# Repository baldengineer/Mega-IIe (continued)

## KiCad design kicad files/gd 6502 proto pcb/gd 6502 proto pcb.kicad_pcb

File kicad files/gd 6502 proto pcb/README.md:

## gd 6502 proto pcb
6502 board is designed for a WDC W65c02 with a QFP footprint. It has a single socket for an EPROM and is wired like the IIc's EEPROM. The `Address` and `Data` headers are meant to connect to the MEGA-II proto board. Other control signals are broken out to other headers.

Runs off of 5V.

## Rev1 Notes:
* Nothing... yet :)

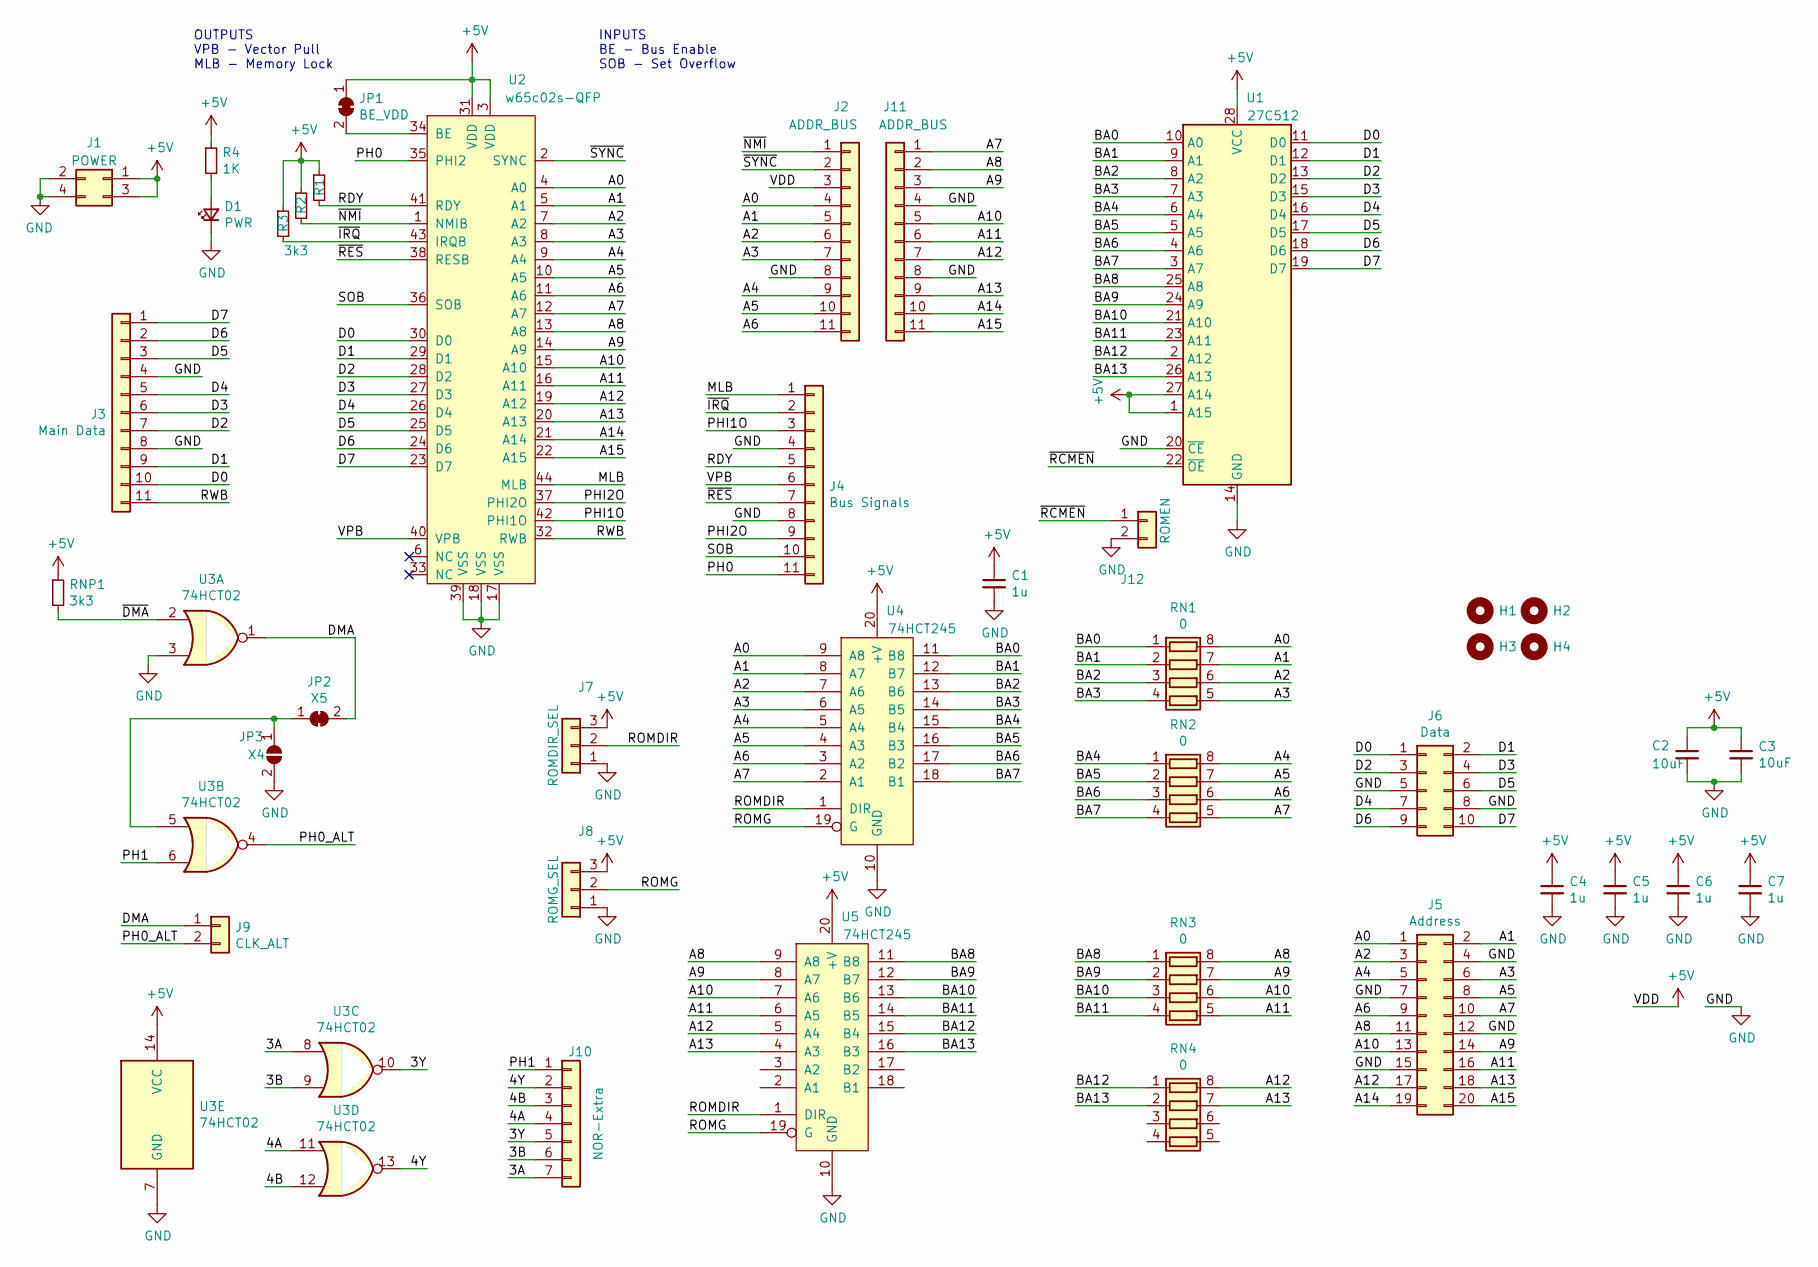
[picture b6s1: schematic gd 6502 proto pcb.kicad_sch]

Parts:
C1, C4, C5, C6, C7: 1u; C_0805_2012Metric
C2: 10uF; C_Radial_D6.3mm_H5.0mm_P2.50mm
C3: 10uF; C_0805_2012Metric
D1: PWR; D_1206_3216Metric
H1, H2, H3, H4: MountingHole; MountingHole_2.7mm_M2.5
J1: POWER; PinHeader_2x02_P2.54mm_Vertical
J2, J11: ADDR_BUS; PinHeader_1x11_P2.54mm_Vertical
J3: Main Data; PinHeader_1x11_P2.54mm_Vertical
J4: Bus Signals; PinHeader_1x11_P2.54mm_Vertical
J5: Address; PinHeader_2x10_P2.54mm_Vertical
J6: Data; PinHeader_2x05_P2.54mm_Vertical
J7: ROMDIR_SEL; PinHeader_1x03_P2.54mm_Vertical
J8: ROMG_SEL; PinHeader_1x03_P2.54mm_Vertical
J9: CLK_ALT; PinHeader_1x02_P2.54mm_Vertical
J10: NOR-Extra; PinHeader_1x07_P2.54mm_Vertical
J12: ROMEN; PinHeader_1x02_P2.54mm_Vertical
JP1: BE_VDD; SolderJumper-2_P1.3mm_Bridged_Pad1.0x1.5mm
JP2: X5; SolderJumper-2_P1.3mm_Bridged_Pad1.0x1.5mm
JP3: X4; SolderJumper-2_P1.3mm_Open_RoundedPad1.0x1.5mm
R1, R2, R3: 3k3; R_0805_2012Metric
R4: 1K; R_0805_2012Metric
RN1, RN2, RN3, RN4: 0; R_Array_Convex_4x0612
RNP1: 3k3; R_0805_2012Metric
U1: 27C512; DIP-28_W15.24mm_Socket_LongPads
U2: w65c02s-QFP; PQFP-44_10x10mm_P0.8mm
U3: 74HCT02; SOIC-14_3.9x8.7mm_P1.27mm
U4, U5: 74HCT245; SOIC-20W_7.5x12.8mm_P1.27mm

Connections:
+5V: C1.1, C2.1, C3.1, C4.1, C5.1, C6.1, C7.1, J1.1, J1.3, J2.3, J7.3, J8.3, JP1.1 (A), R1.1, R2.1, R3.1, R4.1, RNP1.1, U1.1 (A15), U1.27 (A14), U1.28 (VCC), U2.3 (VDD), U2.31 (VDD), U3.14 (VCC), U4.20 (+V), U5.20 (+V)
/3A: J10.7, U3.8
/3B: J10.6, U3.9
/3Y: J10.5, U3.10
/4A: J10.4, U3.11
/4B: J10.3, U3.12
/4Y: J10.2, U3.13
/A0: J2.4, J5.1, RN1.8 (R1.2), U2.4 (A0), U4.9 (A8)
/A1: J2.5, J5.2, RN1.7 (R2.2), U2.5 (A1), U4.8 (A7)
/A2: J2.6, J5.3, RN1.6 (R3.2), U2.7 (A2), U4.7 (A6)
/A3: J2.7, J5.6, RN1.5 (R4.2), U2.8 (A3), U4.6 (A5)
/A4: J2.9, J5.5, RN2.8 (R1.2), U2.9 (A4), U4.5 (A4)
/A5: J2.10, J5.8, RN2.7 (R2.2), U2.10 (A5), U4.4 (A3)
/A6: J2.11, J5.9, RN2.6 (R3.2), U2.11 (A6), U4.3 (A2)
/A7: J5.10, J11.1, RN2.5 (R4.2), U2.12 (A7), U4.2 (A1)
/A8: J5.11, J11.2, RN3.8 (R1.2), U2.13 (A8), U5.9 (A8)
/A9: J5.14, J11.3, RN3.7 (R2.2), U2.14 (A9), U5.8 (A7)
/A10: J5.13, J11.5, RN3.6 (R3.2), U2.15 (A10), U5.7 (A6)
/A11: J5.16, J11.6, RN3.5 (R4.2), U2.16 (A11), U5.6 (A5)
/A12: J5.17, J11.7, RN4.8 (R1.2), U2.19 (A12), U5.5 (A4)
/A13: J5.18, J11.9, RN4.7 (R2.2), U2.20 (A13), U5.4 (A3)
/A14: J5.19, J11.10, U2.21 (A14)
/A15: J5.20, J11.11, U2.22 (A15)
/BA0: RN1.1 (R1.1), U1.10 (A0), U4.11 (B8)
/BA1: RN1.2 (R2.1), U1.9 (A1), U4.12 (B7)
/BA2: RN1.3 (R3.1), U1.8 (A2), U4.13 (B6)
/BA3: RN1.4 (R4.1), U1.7 (A3), U4.14 (B5)
/BA4: RN2.1 (R1.1), U1.6 (A4), U4.15 (B4)
/BA5: RN2.2 (R2.1), U1.5 (A5), U4.16 (B3)
/BA6: RN2.3 (R3.1), U1.4 (A6), U4.17 (B2)
/BA7: RN2.4 (R4.1), U1.3 (A7), U4.18 (B1)
/BA8: RN3.1 (R1.1), U1.25 (A8), U5.11 (B8)
/BA9: RN3.2 (R2.1), U1.24 (A9), U5.12 (B7)
/BA10: RN3.3 (R3.1), U1.21 (A10), U5.13 (B6)
/BA11: RN3.4 (R4.1), U1.23 (A11), U5.14 (B5)
/BA12: RN4.1 (R1.1), U1.2 (A12), U5.15 (B4)
/BA13: RN4.2 (R2.1), U1.26 (A13), U5.16 (B3)
/D0: J3.10, J6.1, U1.11 (D0), U2.30 (D0)
/D1: J3.9, J6.2, U1.12 (D1), U2.29 (D1)
/D2: J3.7, J6.3, U1.13 (D2), U2.28 (D2)
/D3: J3.6, J6.4, U1.15 (D3), U2.27 (D3)
/D4: J3.5, J6.7, U1.16 (D4), U2.26 (D4)
/D5: J3.3, J6.6, U1.17 (D5), U2.25 (D5)
/D6: J3.2, J6.9, U1.18 (D6), U2.24 (D6)
/D7: J3.1, J6.10, U1.19 (D7), U2.23 (D7)
/DMA: J9.1, JP2.2 (B), U3.1
/MLB: J4.1, U2.44 (MLB)
/PH0: J4.11, U2.35 (PHI2)
/PH0_ALT: J9.2, U3.4
/PH1: J10.1, U3.6
/PHI1O: J4.3, U2.42 (PHI1O)
/PHI2O: J4.9, U2.37 (PHI2O)
/RDY: J4.5, R1.2, U2.41 (RDY)
/ROMDIR: J7.2, U4.1 (DIR), U5.1 (DIR)
/ROMG: J8.2, U4.19 (G), U5.19 (G)
/RWB: J3.11, U2.32 (RWB)
/SOB: J4.10, U2.36 (SOB)
/VPB: J4.6, U2.40 (VPB)
/~DMA: RNP1.2, U3.2
/~IRQ: J4.2, R3.2, U2.43 (IRQB)
/~NMI: J2.1, R2.2, U2.1 (NMIB)
/~RCMEN: J12.1, U1.22 (~OE)
/~RES: J4.7, U2.38 (RESB)
/~SYNC: J2.2, U2.2 (SYNC)
GND: C1.2, C2.2, C3.2, C4.2, C5.2, C6.2, C7.2, D1.1 (K), J1.2, J1.4, J2.8, J3.4, J3.8, J4.4, J4.8, J5.4, J5.7, J5.12, J5.15, J6.5, J6.8, J7.1, J8.1, J11.4, J11.8, J12.2, JP3.2 (B), U1.14 (GND), U1.20 (~CE), U2.17 (VSS), U2.18 (VSS), U2.39 (VSS), U3.3, U3.7 (GND), U4.10 (GND), U5.10 (GND)
unnamed: D1.2 (A), R4.2
unnamed: JP1.2 (B), U2.34 (BE)
unnamed: JP2.1 (A), JP3.1 (A), U3.5

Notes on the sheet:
INPUTS BE - Bus Enable SOB - Set Overflow
OUTPUTS VPB - Vector Pull MLB - Memory Lock

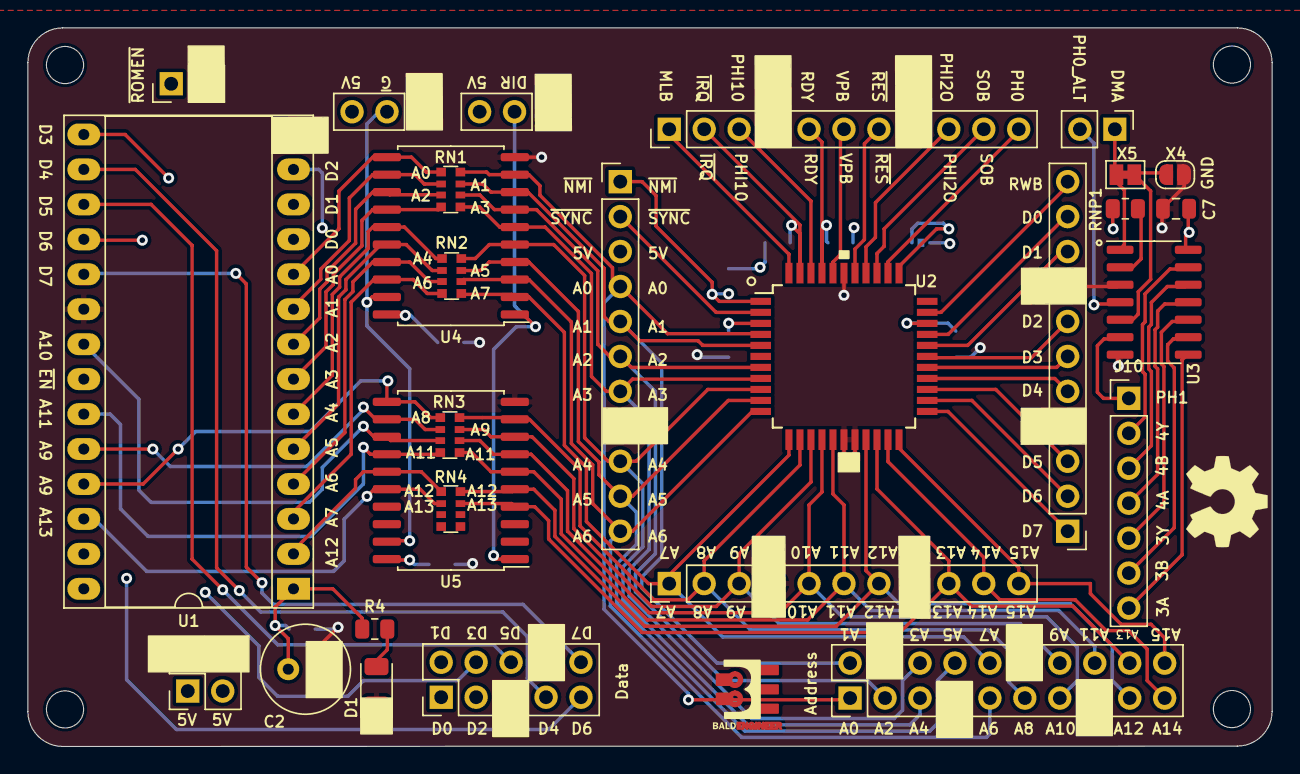
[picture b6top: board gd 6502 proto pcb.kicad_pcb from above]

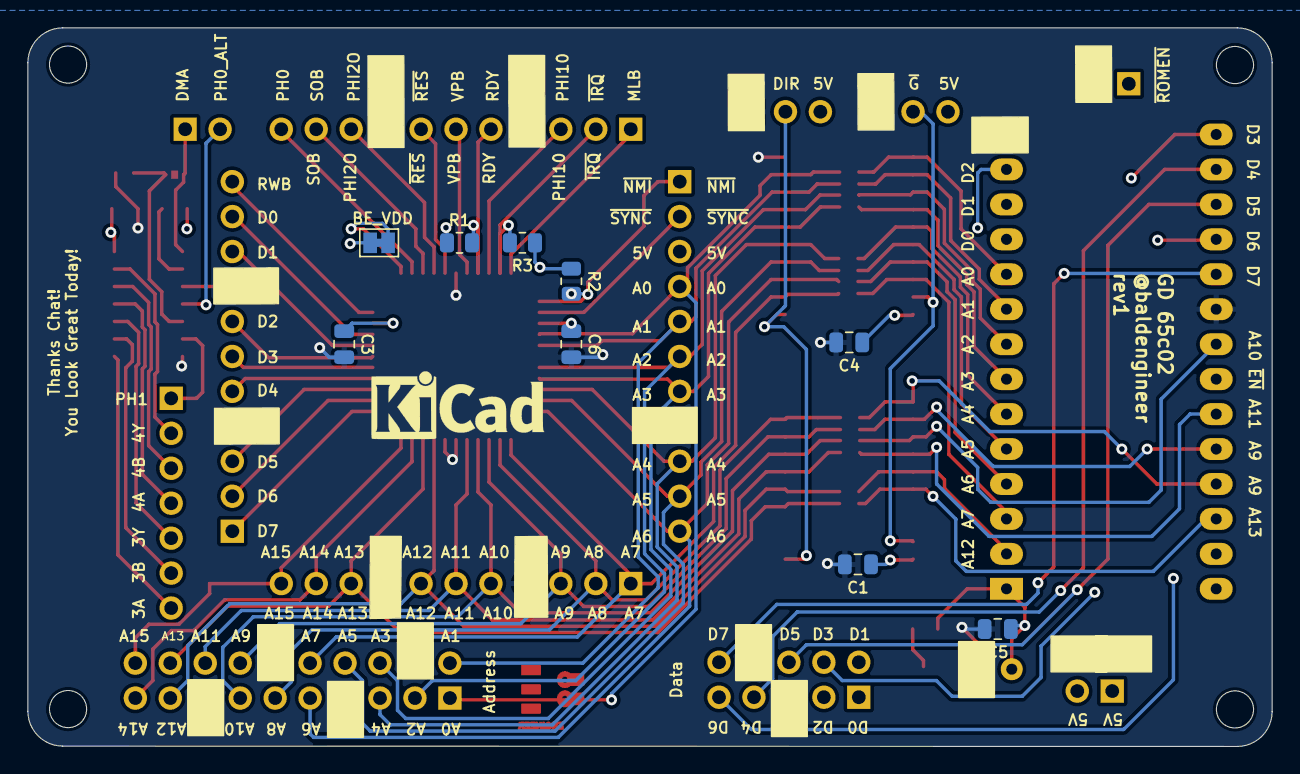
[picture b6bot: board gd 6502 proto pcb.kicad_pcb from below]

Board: 4 copper layers, 90.4 x 52.2 mm, 42 parts (9 on the bottom side), 68 nets.

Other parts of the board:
He: MountingHole; MountingHole_2.7mm_M2.5
svg2mod: G***; BE5v2

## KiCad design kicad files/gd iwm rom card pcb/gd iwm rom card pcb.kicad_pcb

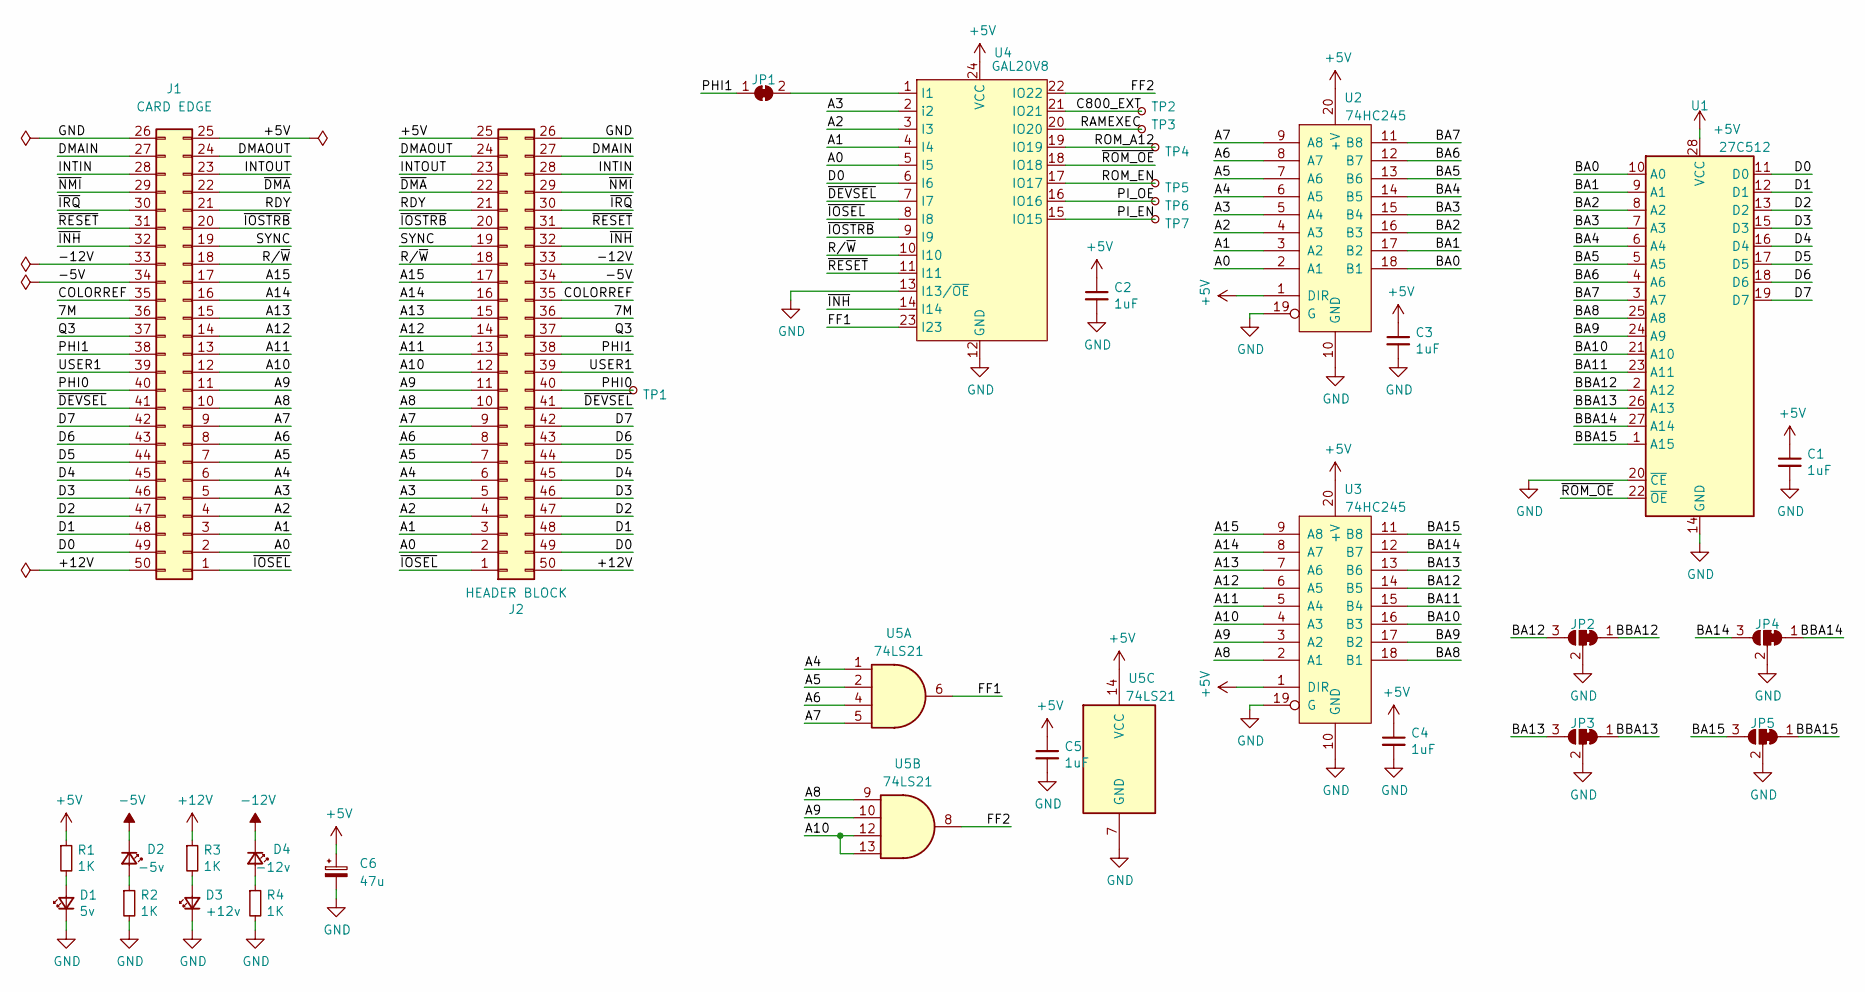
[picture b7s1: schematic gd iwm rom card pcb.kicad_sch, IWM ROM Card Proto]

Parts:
C1, C2, C3, C4, C5: 1uF; C_0805_2012Metric
C6: 47u; CP_Radial_D5.0mm_P2.50mm
D1: 5v; LED_1206_3216Metric
D2: -5v; LED_1206_3216Metric
D3: +12v; LED_1206_3216Metric
D4: -12v; LED_1206_3216Metric
J1: CARD EDGE; AppleII_Bus
J2: HEADER BLOCK; PinSocket_2x25_P2.54mm_Vertical_CCW_Mirrored_NoSilk
JP1: PH; SolderJumper-2_P1.3mm_Bridged_RoundedPad1.0x1.5mm
JP2, JP3, JP4, JP5: SolderJumper_3_Bridged12; SolderJumper-3_P1.3mm_Bridged12_RoundedPad1.0x1.5mm_NumberL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
R1, R2, R3, R4: 1K; R_0805_2012Metric
TP1, TP4, TP5, TP6, TP7: PH0; TestPoint_Pad_1.0x1.0mm
TP2: IO21; TestPoint_Pad_1.0x1.0mm
TP3: IO20; TestPoint_Pad_1.0x1.0mm
U1: 27C512; DIP_Socket-28_W11.9_W12.7_W15.24_W17.78_W18.5_3M_228-1277-0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
U2, U3: 74HC245; SOIC-20W_7.5x12.8mm_P1.27mm
U4: GAL20V8; DIP-24_W7.62mm_Socket_LongPads
U5: 74LS21; SO-14_3.9x8.65mm_P1.27mm

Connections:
+5V: C1.1, C2.1, C3.1, C4.1, C5.1, C6.1, J1.25, J2.25, R1.1, U1.28 (VCC), U2.1 (DIR), U2.20 (+V), U3.1 (DIR), U3.20 (+V), U4.24 (VCC), U5.14 (VCC)
+12V: J1.50, J2.50, R3.1
-5V: D2.1 (K), J1.34, J2.34
-12V: D4.1 (K), J1.33, J2.33
/7M: J1.36, J2.36
/A0: J1.2, J2.2, U2.2 (A1), U4.5 (I5)
/A1: J1.3, J2.3, U2.3 (A2), U4.4 (I4)
/A2: J1.4, J2.4, U2.4 (A3), U4.3 (I3)
/A3: J1.5, J2.5, U2.5 (A4), U4.2 (i2)
/A4: J1.6, J2.6, U2.6 (A5), U5.1
/A5: J1.7, J2.7, U2.7 (A6), U5.2
/A6: J1.8, J2.8, U2.8 (A7), U5.4
/A7: J1.9, J2.9, U2.9 (A8), U5.5
/A8: J1.10, J2.10, U3.2 (A1), U5.9
/A9: J1.11, J2.11, U3.3 (A2), U5.10
/A10: J1.12, J2.12, U3.4 (A3), U5.12, U5.13
/A11: J1.13, J2.13, U3.5 (A4)
/A12: J1.14, J2.14, U3.6 (A5)
/A13: J1.15, J2.15, U3.7 (A6)
/A14: J1.16, J2.16, U3.8 (A7)
/A15: J1.17, J2.17, U3.9 (A8)
/BA0: U1.10 (A0), U2.18 (B1)
/BA1: U1.9 (A1), U2.17 (B2)
/BA2: U1.8 (A2), U2.16 (B3)
/BA3: U1.7 (A3), U2.15 (B4)
/BA4: U1.6 (A4), U2.14 (B5)
/BA5: U1.5 (A5), U2.13 (B6)
/BA6: U1.4 (A6), U2.12 (B7)
/BA7: U1.3 (A7), U2.11 (B8)
/BA8: U1.25 (A8), U3.18 (B1)
/BA9: U1.24 (A9), U3.17 (B2)
/BA10: U1.21 (A10), U3.16 (B3)
/BA11: U1.23 (A11), U3.15 (B4)
/BA12: JP2.3 (B), U3.14 (B5)
/BA13: JP3.3 (B), U3.13 (B6)
/BA14: JP4.3 (B), U3.12 (B7)
/BA15: JP5.3 (B), U3.11 (B8)
/BBA12: JP2.1 (A), U1.2 (A12)
/BBA13: JP3.1 (A), U1.26 (A13)
/BBA14: JP4.1 (A), U1.27 (A14)
/BBA15: JP5.1 (A), U1.1 (A15)
/C800_EXT: TP2.1, U4.21 (IO21)
/COLORREF: J1.35, J2.35
/D0: J1.49, J2.49, U1.11 (D0), U4.6 (I6)
/D1: J1.48, J2.48, U1.12 (D1)
/D2: J1.47, J2.47, U1.13 (D2)
/D3: J1.46, J2.46, U1.15 (D3)
/D4: J1.45, J2.45, U1.16 (D4)
/D5: J1.44, J2.44, U1.17 (D5)
/D6: J1.43, J2.43, U1.18 (D6)
/D7: J1.42, J2.42, U1.19 (D7)
/DMAIN: J1.27, J2.27
/DMAOUT: J1.24, J2.24
/FF1: U4.23 (I23), U5.6
/FF2: U4.22 (IO22), U5.8
/INTIN: J1.28, J2.28
/INTOUT: J1.23, J2.23
/PHI0: J1.40, J2.40, TP1.1
/PHI1: J1.38, J2.38, JP1.1 (A)
/PI_EN: TP7.1, U4.15 (IO15)
/PI_OE: TP6.1, U4.16 (IO16)
/Q3: J1.37, J2.37
/RAMEXEC: TP3.1, U4.20 (IO20)
/RDY: J1.21, J2.21
/ROM_A12: TP4.1, U4.19 (IO19)
/ROM_EN: TP5.1, U4.17 (IO17)
/R/~W: J1.18, J2.18, U4.10 (I10)
/SYNC: J1.19, J2.19
/USER1: J1.39, J2.39
/~DEVSEL: J1.41, J2.41, U4.7 (I7)
/~DMA: J1.22, J2.22
/~INH: J1.32, J2.32, U4.14 (I14)
/~IOSEL: J1.1, J2.1, U4.8 (I8)
/~IOSTRB: J1.20, J2.20, U4.9 (I9)
/~IRQ: J1.30, J2.30
/~NMI: J1.29, J2.29
/~RESET: J1.31, J2.31, U4.11 (I11)
/~ROM_OE: U1.22 (~OE), U4.18 (IO18)
GND: C1.2, C2.2, C3.2, C4.2, C5.2, C6.2, D1.1 (K), D3.1 (K), J1.26, J2.26, JP2.2 (C), JP3.2 (C), JP4.2 (C), JP5.2 (C), R2.2, R4.2, U1.14 (GND), U1.20 (~CE), U2.10 (GND), U2.19 (G), U3.10 (GND), U3.19 (G), U4.12 (GND), U4.13 (I13/~OE), U5.7 (GND)
unnamed: D1.2 (A), R1.2
unnamed: D2.2 (A), R2.1
unnamed: D3.2 (A), R3.2
unnamed: D4.2 (A), R4.1
unnamed: JP1.2 (B), U4.1 (I1)

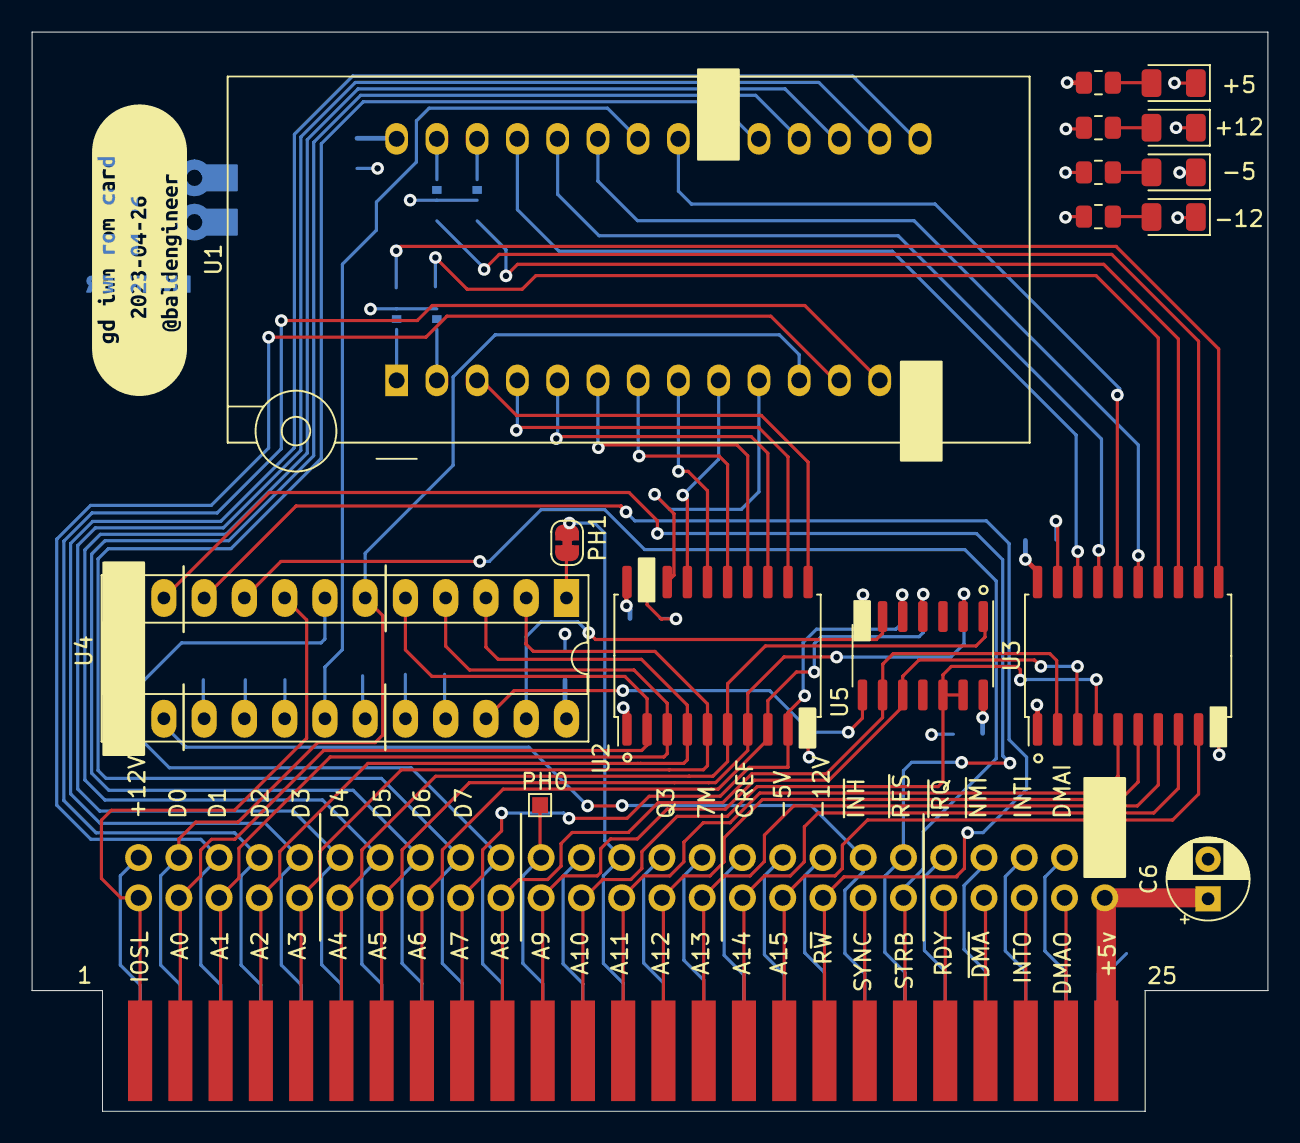
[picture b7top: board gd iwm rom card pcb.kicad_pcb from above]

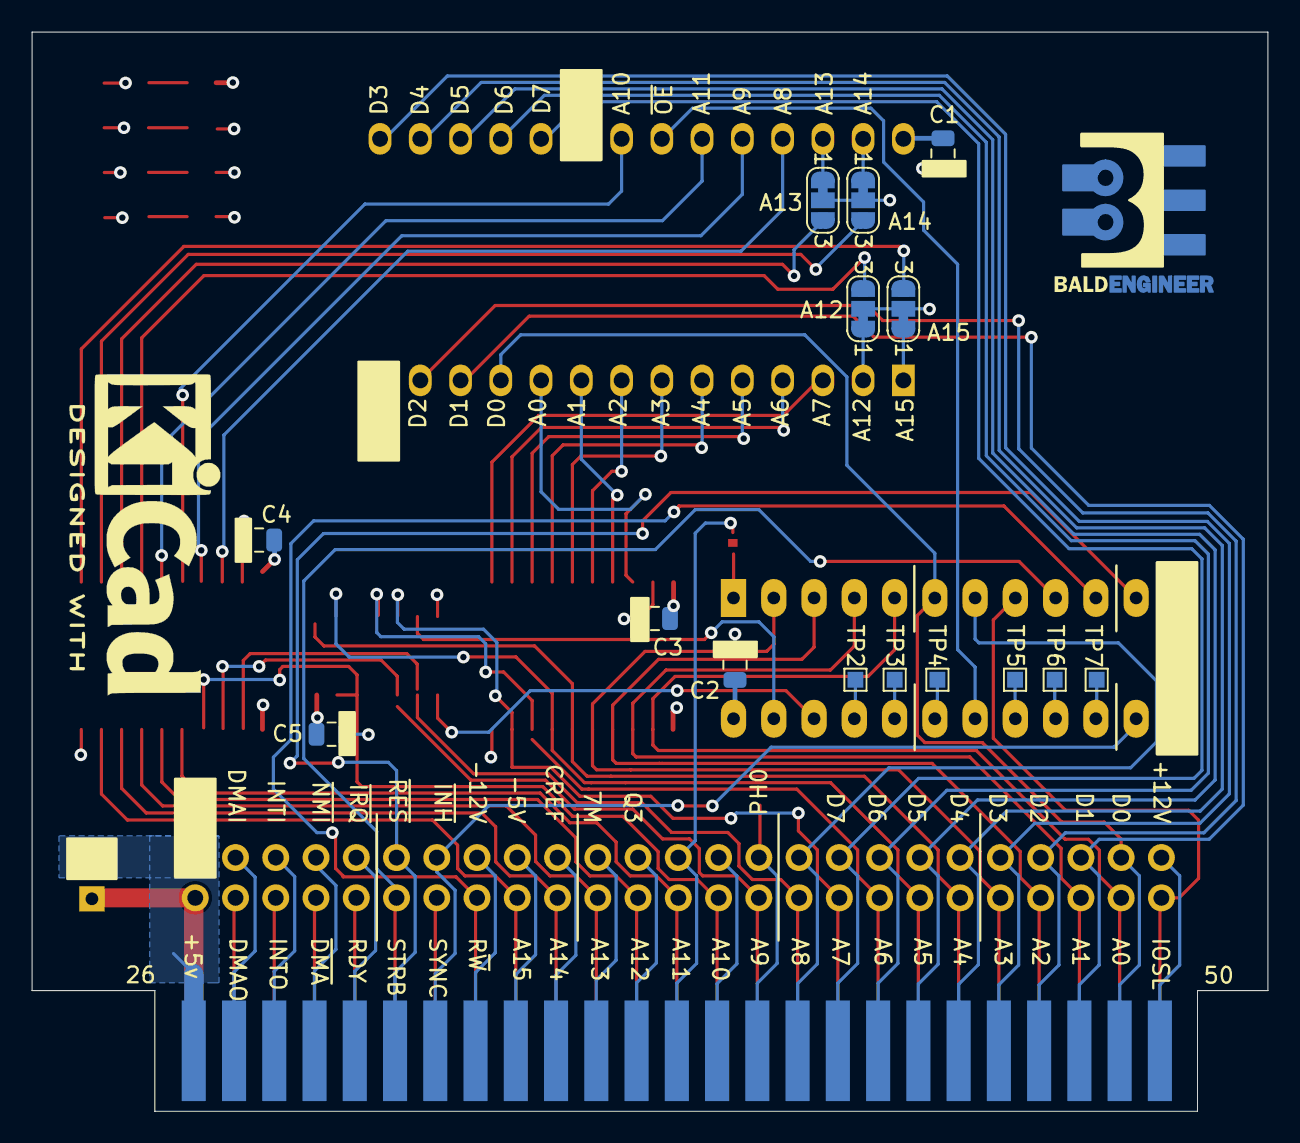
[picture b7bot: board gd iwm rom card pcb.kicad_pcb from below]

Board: 4 copper layers, 78.0 x 68.1 mm, 35 parts (16 on the bottom side), 84 nets.

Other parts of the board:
kibuzzard-644A2244: G***; kibuzzard-644A2244
svg2mod: G***; BE10v2

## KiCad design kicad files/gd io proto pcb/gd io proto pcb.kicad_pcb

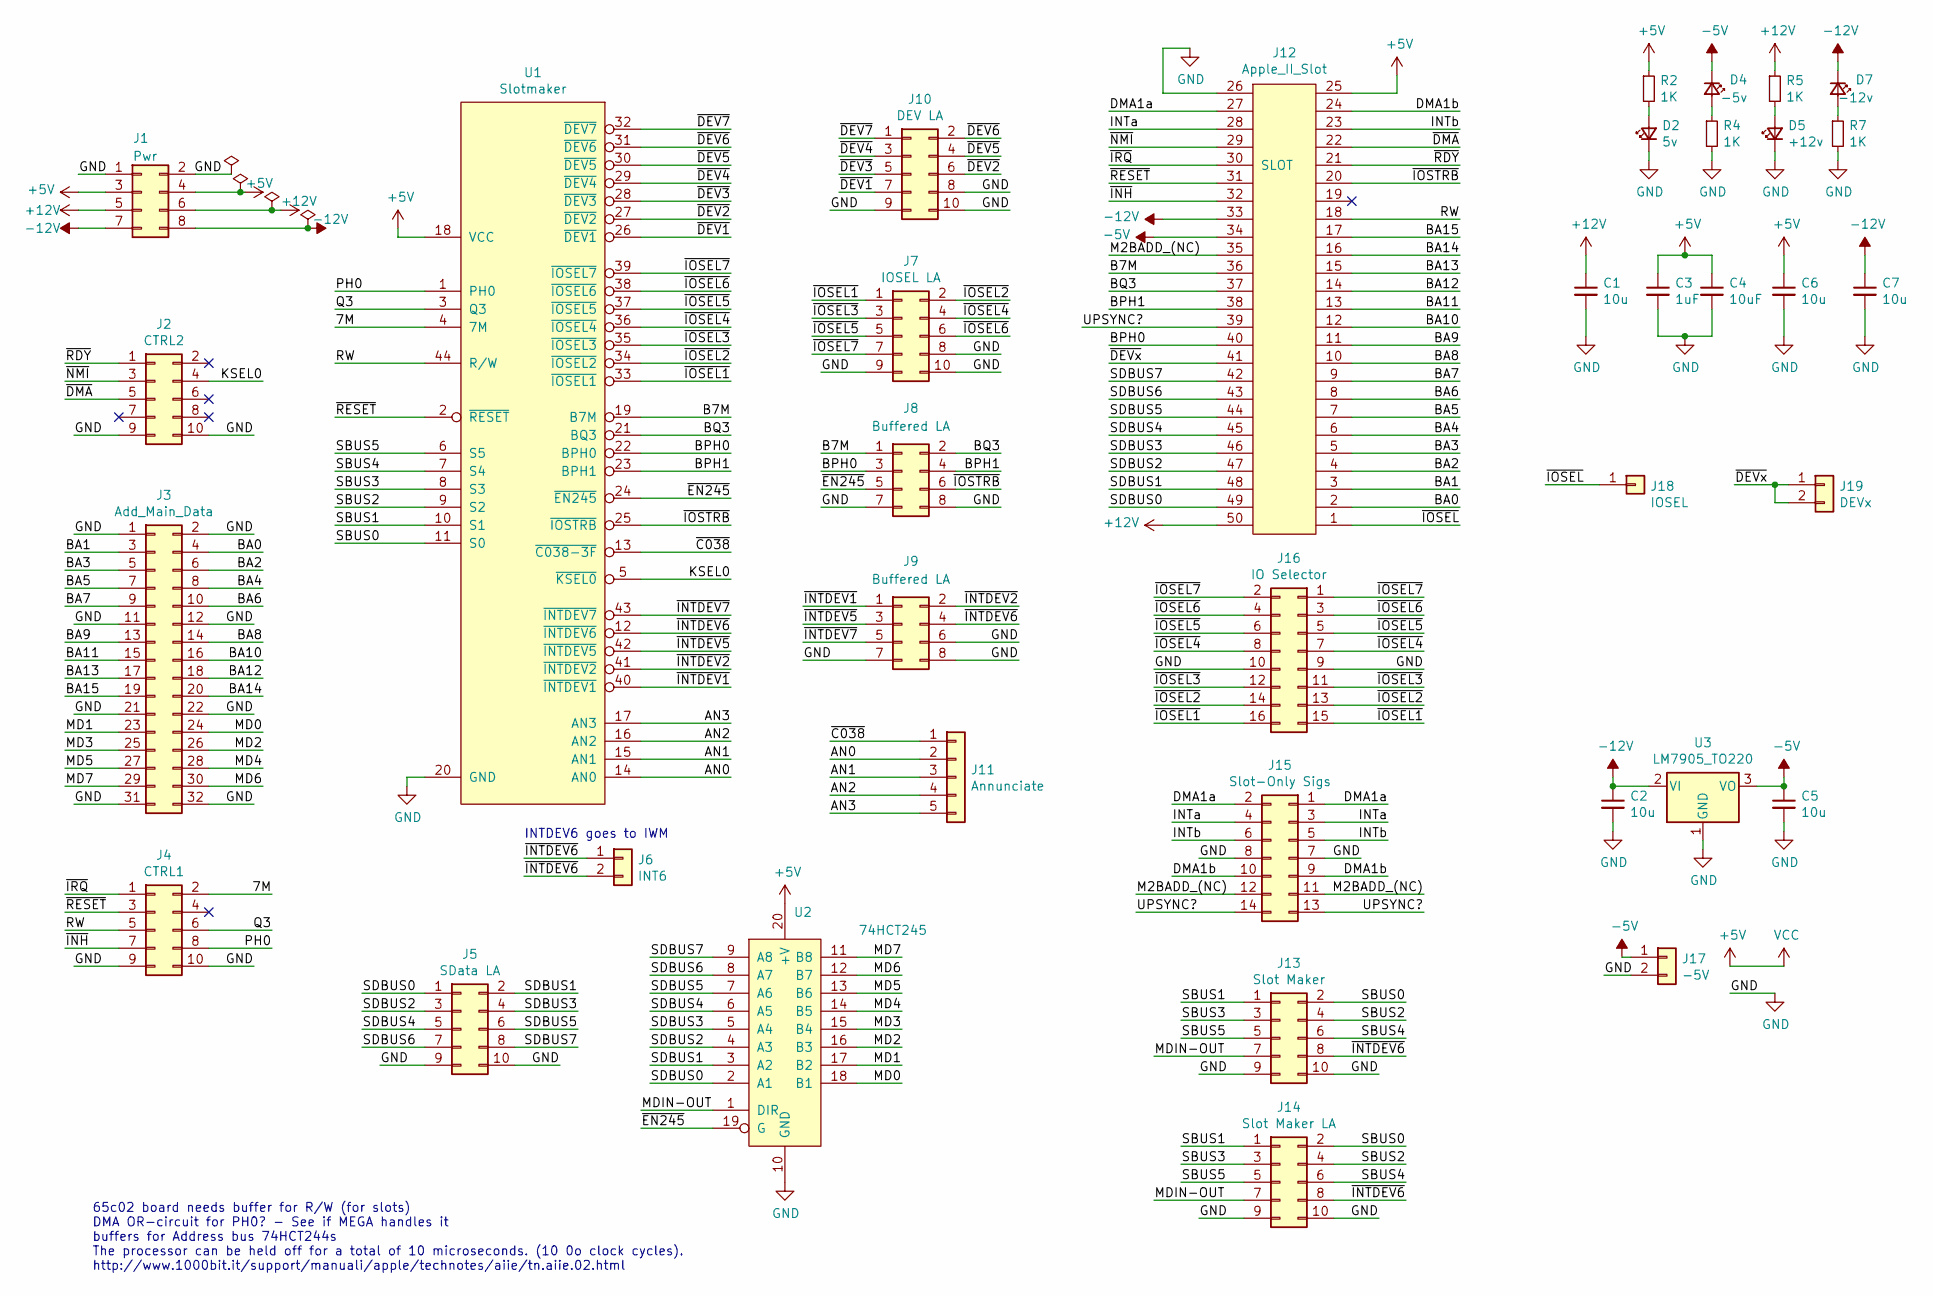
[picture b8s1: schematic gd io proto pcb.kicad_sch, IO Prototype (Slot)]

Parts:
C1, C2, C5, C6, C7: 10u; C_0805_2012Metric
C3: 1uF; C_0805_2012Metric
C4: 10uF; C_0805_2012Metric
D2: 5v; LED_1206_3216Metric
D4: -5v; LED_1206_3216Metric
D5: +12v; LED_1206_3216Metric
D7: -12v; LED_1206_3216Metric
J1: Pwr; PinHeader_2x04_P2.54mm_Horizontal
J2: CTRL2; PinHeader_2x05_P2.54mm_Horizontal
J3: Add_Main_Data; PinHeader_2x16_P2.54mm_Horizontal
J4: CTRL1; PinHeader_2x05_P2.54mm_Horizontal
J5: SData LA; PinSocket_2x05_P2.54mm_Vertical
J6: INT6; PinHeader_1x02_P2.54mm_Vertical-LOCK
J7: IOSEL LA; PinSocket_2x05_P2.54mm_Vertical
J8, J9: Buffered LA; PinSocket_2x04_P2.54mm_Vertical
J10: DEV LA; PinSocket_2x05_P2.54mm_Vertical
J11: Annunciate; PinHeader_1x05_P2.54mm_Vertical-LOCK
J12: Apple_II_Slot; Amp_2358256-4_50pos_right_angle_card
J13: Slot Maker; PinSocket_2x05_P2.54mm_Vertical
J14: Slot Maker LA; PinSocket_2x05_P2.54mm_Vertical
J15: Slot-Only Sigs; PinSocket_2x07_P2.54mm_Vertical
J16: IO Selector; PinSocket_2x08_P2.54mm_Vertical
J17: -5V; PinHeader_1x02_P2.54mm_Vertical-LOCK
J18: IOSEL; PinHeader_1x01_P2.54mm_Vertical
J19: DEVx; PinHeader_1x02_P2.54mm_Vertical
R2, R4, R5, R7: 1K; R_0805_2012Metric
U1: Slotmaker; PLCC-44_THT-Socket
U2: 74HCT245; SO-20_12.8x7.5mm_P1.27mm
U3: LM7905_TO220; TO-220-3_Vertical

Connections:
+5V: C3.1, C4.1, C6.1, J1.3, J1.4, J12.25, R2.1, U1.18 (VCC), U2.20 (+V)
+12V: C1.1, J1.5, J1.6, J12.50, R5.1
-5V: C5.1, D4.1 (K), J12.34, J17.1, U3.3 (VO)
-12V: C2.1, C7.1, D7.1 (K), J1.7, J1.8, J12.33, U3.2 (VI)
/7M: J4.2, U1.4 (7M)
/AN0: J11.2, U1.14 (AN0)
/AN1: J11.3, U1.15 (AN1)
/AN2: J11.4, U1.16 (AN2)
/AN3: J11.5, U1.17 (AN3)
/B7M: J8.1, J12.36, U1.19 (B7M)
/BA0: J3.4, J12.2
/BA1: J3.3, J12.3
/BA2: J3.6, J12.4
/BA3: J3.5, J12.5
/BA4: J3.8, J12.6
/BA5: J3.7, J12.7
/BA6: J3.10, J12.8
/BA7: J3.9, J12.9
/BA8: J3.14, J12.10
/BA9: J3.13, J12.11
/BA10: J3.16, J12.12
/BA11: J3.15, J12.13
/BA12: J3.18, J12.14
/BA13: J3.17, J12.15
/BA14: J3.20, J12.16
/BA15: J3.19, J12.17
/BPH0: J8.3, J12.40, U1.22 (BPH0)
/BPH1: J8.4, J12.38, U1.23 (BPH1)
/BQ3: J8.2, J12.37, U1.21 (BQ3)
/DMA1a: J12.27, J15.1, J15.2
/DMA1b: J12.24, J15.9, J15.10
/INTa: J12.28, J15.3, J15.4
/INTb: J12.23, J15.5, J15.6
/KSEL0: J2.4, U1.5 (~KSEL0)
/M2BADD_(NC): J12.35, J15.11, J15.12
/MD0: J3.24, U2.18 (B1)
/MD1: J3.23, U2.17 (B2)
/MD2: J3.26, U2.16 (B3)
/MD3: J3.25, U2.15 (B4)
/MD4: J3.28, U2.14 (B5)
/MD5: J3.27, U2.13 (B6)
/MD6: J3.30, U2.12 (B7)
/MD7: J3.29, U2.11 (B8)
/MDIN-OUT: J13.7, J14.7, U2.1 (DIR)
/PH0: J4.8, U1.1 (PH0)
/Q3: J4.6, U1.3 (Q3)
/RW: J4.5, J12.18, U1.44 (R/W)
/SBUS0: J13.2, J14.2, U1.11 (S0)
/SBUS1: J13.1, J14.1, U1.10 (S1)
/SBUS2: J13.4, J14.4, U1.9 (S2)
/SBUS3: J13.3, J14.3, U1.8 (S3)
/SBUS4: J13.6, J14.6, U1.7 (S4)
/SBUS5: J13.5, J14.5, U1.6 (S5)
/SDBUS0: J5.1, J12.49, U2.2 (A1)
/SDBUS1: J5.2, J12.48, U2.3 (A2)
/SDBUS2: J5.3, J12.47, U2.4 (A3)
/SDBUS3: J5.4, J12.46, U2.5 (A4)
/SDBUS4: J5.5, J12.45, U2.6 (A5)
/SDBUS5: J5.6, J12.44, U2.7 (A6)
/SDBUS6: J5.7, J12.43, U2.8 (A7)
/SDBUS7: J5.8, J12.42, U2.9 (A8)
/UPSYNC?: J12.39, J15.13, J15.14
/~C038: J11.1, U1.13 (~C038-3F)
/~DEV1: J10.7, U1.26 (~DEV1)
/~DEV2: J10.6, U1.27 (~DEV2)
/~DEV3: J10.5, U1.28 (~DEV3)
/~DEV4: J10.3, U1.29 (~DEV4)
/~DEV5: J10.4, U1.30 (~DEV5)
/~DEV6: J10.2, U1.31 (~DEV6)
/~DEV7: J10.1, U1.32 (~DEV7)
/~DEVx: J12.41, J19.1, J19.2
/~DMA: J2.5, J12.22
/~EN245: J8.5, U1.24 (~EN245), U2.19 (G)
/~INH: J4.7, J12.32
/~INTDEV1: J9.1, U1.40 (~INTDEV1)
/~INTDEV2: J9.2, U1.41 (~INTDEV2)
/~INTDEV5: J9.3, U1.42 (~INTDEV5)
/~INTDEV6: J6.1, J6.2, J9.4, J13.8, J14.8, U1.12 (~INTDEV6)
/~INTDEV7: J9.5, U1.43 (~INTDEV7)
/~IOSEL1: J7.1, J16.15, J16.16, U1.33 (~IOSEL1)
/~IOSEL2: J7.2, J16.13, J16.14, U1.34 (~IOSEL2)
/~IOSEL3: J7.3, J16.11, J16.12, U1.35 (~IOSEL3)
/~IOSEL4: J7.4, J16.7, J16.8, U1.36 (~IOSEL4)
/~IOSEL5: J7.5, J16.5, J16.6, U1.37 (~IOSEL5)
/~IOSEL6: J7.6, J16.3, J16.4, U1.38 (~IOSEL6)
/~IOSEL7: J7.7, J16.1, J16.2, U1.39 (~IOSEL7)
/~IOSEL: J12.1, J18.1
/~IOSTRB: J8.6, J12.20, U1.25 (~IOSTRB)
/~IRQ: J4.1, J12.30 (SLOT)
/~NMI: J2.3, J12.29
/~RDY: J2.1, J12.21
/~RESET: J4.3, J12.31, U1.2 (~RESET)
GND: C1.2, C2.2, C3.2, C4.2, C5.2, C6.2, C7.2, D2.1 (K), D5.1 (K), J1.1, J1.2, J2.9, J2.10, J3.1, J3.2, J3.11, J3.12, J3.21, J3.22, J3.31, J3.32, J4.9, J4.10, J5.9, J5.10, J7.8, J7.9, J7.10, J8.7, J8.8, J9.6, J9.7, J9.8, J10.8, J10.9, J10.10, J12.26, J13.9, J13.10, J14.9, J14.10, J15.7, J15.8, J16.9, J16.10, J17.2, R4.2, R7.2, U1.20 (GND), U2.10 (GND), U3.1 (GND)
unnamed: D2.2 (A), R2.2
unnamed: D4.2 (A), R4.1
unnamed: D5.2 (A), R5.2
unnamed: D7.2 (A), R7.1

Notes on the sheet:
INTDEV6 goes to IWM
65c02 board needs buffer for R/W (for slots) DMA OR-circuit for PH0? - See if MEGA handles it buffers for Address bus 74HCT244s The processor can be held off for a total of 10 microseconds. (10 0o clock cycles). http://www.1000bit.it/support/manuali/apple/technotes/aiie/tn.aiie.02.html

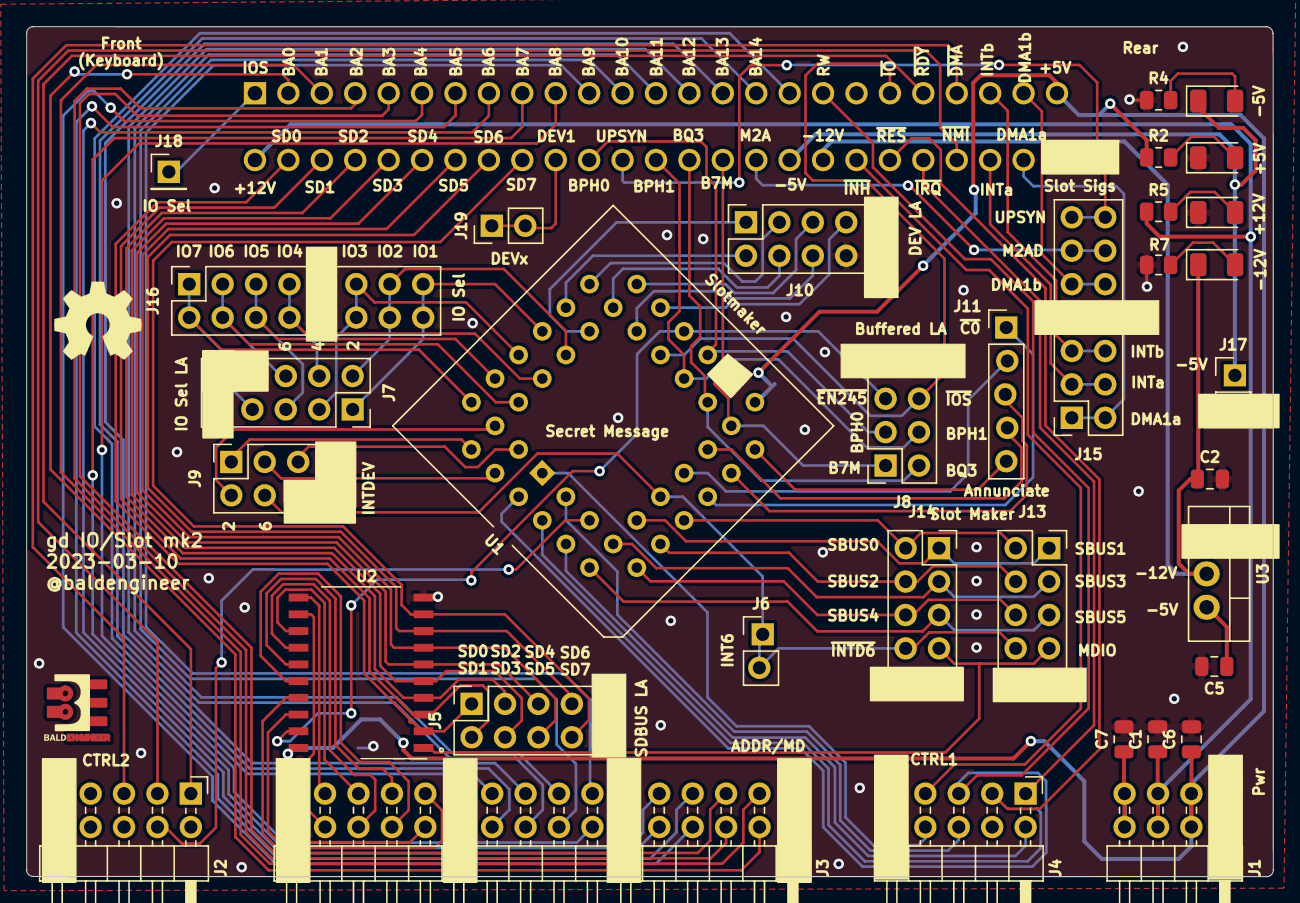
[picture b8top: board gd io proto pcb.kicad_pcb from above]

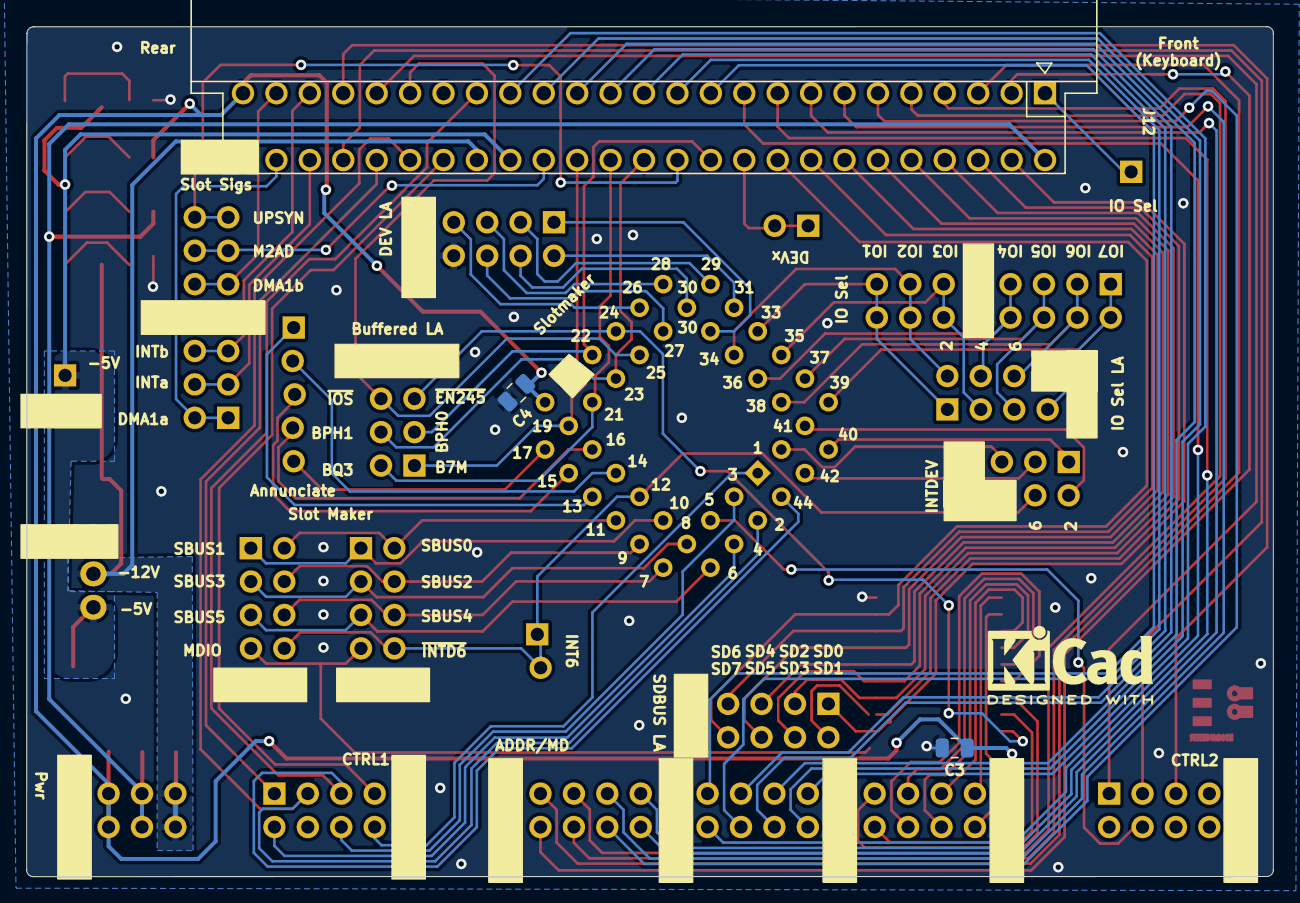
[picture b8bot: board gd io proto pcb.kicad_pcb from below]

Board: 2 copper layers, 94.8 x 64.6 mm, 38 parts (3 on the bottom side), 97 nets.

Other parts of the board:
svg2mod: G***; BE5v2

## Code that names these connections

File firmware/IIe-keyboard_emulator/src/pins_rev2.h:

// Pin mapping for Mega IIe Rev 2, KBD2040 Rev 3
// Not confusing at all.

// DO NOT FORGET TO CHANGE PINOUTS IN THE PIO!

// Pins
// Corrected data bus on rev2
#define KSEL0  25
#define   MD0  3
#define   MD1  4
#define   MD2  5
#define   MD3  6
#define   MD4  7
#define   MD5  8
#define   MD6  9
#define   MD7 10
// EN_245 11
// RESET 12
#define KSEL1 13
#define KSEL2 14
#define    RW 15
#define   PH0 16
#define RESET_CTL 18
#define COLOR_MODE_PIN 22

// Free pins
// 17, 19, 21

// IO Pins
//const uint LED_PIN = PICO_DEFAULT_LED_PIN;  // its the LED pin (that we don't have)
#define   DEBUG_PIN 24
#define   enable_245_pin 11
#define   OAPL_pin 20
#define   CAPL_pin 23

// Power Sequencing
#define   MEGA_POWER 29   // output! (was an input, that changed.) 
#define   ANALOG_POWER 28 // output 
// On Mega Rev3, only two pins were available for power sequence
//#define  Enable_p12V 27   // output
//#define  Enable_n12V 28   // output
//#define   Enable_p5V 29   // output
// PWR_SEQ_MASK was... (29,28,27)
// 0x3800 0000


// 0011 0000 0000 0000 
#define PWR_SEQ_MASK 0x30000000  // should match 29,28

#define      PRESSED 0x0
#define  NOT_PRESSED 0x1
#define      PWR_OFF 0x0
#define       PWR_ON 0x1
#define   PWR_TOGGLE 0x2
